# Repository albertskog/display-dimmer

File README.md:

# Display Dimmer

A pair of physical buttons to control the brightness of a pair of external monitors over HDMI.

## Why?

My USB-C port replicator does not pass on brightness commands to my monitors.

## How?

HDMI has a control channel called DDC. Hook this board up to a spare HDMI port on a monitor and use the buttons to control the brightness.

# Hardware Considerations

Here are some design considerations that were taken into account.

## VCC Voltage

The board has a footprint for a 3.3 V regulator and also a footprint for a 0 Ohm bypass to use 5 V directly from USB. HDMI signaling is 5 V and the CH32V003 can run at 5 V, but both also work at 3.3 V. I have used the 5 V option.

## Pull-up Resistors

On my monitors, the I2C lines are already pulled up to 5 V internally. The PCB has footprints for additional pull-up, but I found it works fine without populating them.

## USB

The board has a USB connector for power. The data lines are connected to GPIO pins for possible future use.

> Only GPIOs 0-4 can be used for USB D+/D- due to limits of the [c.andi](https://msyksphinz-self.github.io/riscv-isadoc/html/rvc.html#c-andi) instruction which can only hold a 5 bit value.
> You **cannot use** PC5-PC7 and PD5-PD7 for D+/D-!

[GitHub - cnlohr/rv003usb: CH32V003 RISC-V Pure Software USB Controller](https://github.com/cnlohr/rv003usb)

## BOM

| Amount | Part                | Name         | Source                                                                  |
|--------|---------------------|--------------|-------------------------------------------------------------------------|
| 1x     | MCU                 | CH32V003F4P6 | WCH on Aliexpress                                                       |
| 2x     | HDMI connector      | 685119134923 | [Electrokit](https://www.electrokit.com/hdmi-hona-19p-pcb-smd-wrth)     |
| 1x     | Micro USB connector | 629105136821 | [Electrokit](https://www.electrokit.com/usb-micro-b-kontakt-smd)        |
| 2x     | Buttons             | MX-style     |                                                                         |
| 1x     | Fuse                | 1206L025YR   | [Electrokit](https://www.electrokit.com/polyswitch-16v-0.25a-smd)       |
| 4x     | Protection resistor | 1206 22R     |                                                                         |
| 2x     | ESD protection      | NUP2105LT1G  | [Electrokit](https://www.electrokit.com/nup2105lt1g-sot23-3-tvs-diod)   |
| 1x     | 5 V bypass          | 1206 0R      |                                                                         |

### Not mounted

| Amount | Part                | Name         | Source                                                                                    |
|--------|---------------------|--------------|-------------------------------------------------------------------------------------------|
| 4x     | Pull-up resistor    | 1206 10K     |                                                                                           |
| 1x     | 3.3 V LDO           | LDI1117-3.3H | [Electrokit](https://www.electrokit.com/ldi1117-3.3h-sot-223-spanningsregulator-ldo-3.3v) |
| 1x     | Crystal 24 MHz      | HC49/U4H     | [Electrokit](https://www.electrokit.com/kristall-24.000mhz-smd-hc49/u4h)                  |

# Firmware

There are three firmware options:

1. The proof-of-concept written in Micropython on a Raspberry Pi RP2040.
2. The prototype firmware written in Platformio/Arduino C++ on a WCH CH32V003 devkit.
3. The final firmware written in Rust on the custom PCB.

## DDC Commands

DDC commands are hard-coded in the firmware. The payloads were generated from a slightly modified version of [python-ddcci](https://github.com/Informatic/python-ddcci)

| Command       | Data                                          |
|---------------|-----------------------------------------------|
| Set 0%        | `[0x51, 0x84, 0x3, 0x10, 0x0, 0x0, 0xa8]`     |
| Set 10%       | `[0x51, 0x84, 0x3, 0x10, 0x0, 0xa, 0xa2]`     |
| Set 20%       | `[0x51, 0x84, 0x3, 0x10, 0x0, 0x14, 0xbc]`    |
| Set 30%       | `[0x51, 0x84, 0x3, 0x10, 0x0, 0x1e, 0xb6]`    |
| Set 40%       | `[0x51, 0x84, 0x3, 0x10, 0x0, 0x28, 0x80]`    |
| Set 50%       | `[0x51, 0x84, 0x3, 0x10, 0x0, 0x32, 0x9a]`    |
| Set 60%       | `[0x51, 0x84, 0x3, 0x10, 0x0, 0x3c, 0x94]`    |
| Set 70%       | `[0x51, 0x84, 0x3, 0x10, 0x0, 0x46, 0xee]`    |
| Set 80%       | `[0x51, 0x84, 0x3, 0x10, 0x0, 0x50, 0xf8]`    |
| Set 90%       | `[0x51, 0x84, 0x3, 0x10, 0x0, 0x5a, 0xf2]`    |
| Set 100%      | `[0x51, 0x84, 0x3, 0x10, 0x0, 0x64, 0xcc]`    |
| Get (not used)| `[0x51, 0x82, 0x1, 0x10, 0xad]`               |

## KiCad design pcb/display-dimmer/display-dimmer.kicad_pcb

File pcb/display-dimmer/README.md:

# Display Dimmer PCB

This folder contains the Kicad project files for the Display Dimmer PCB.

Unfortunatley, a couple of footprints from SnapEDA were used without realizing their license does not permit sharing. You will need to download them separatley:

- USB connector: https://www.digikey.se/en/models/2627271
- HDMI connector: https://www.digikey.se/en/models/2508506

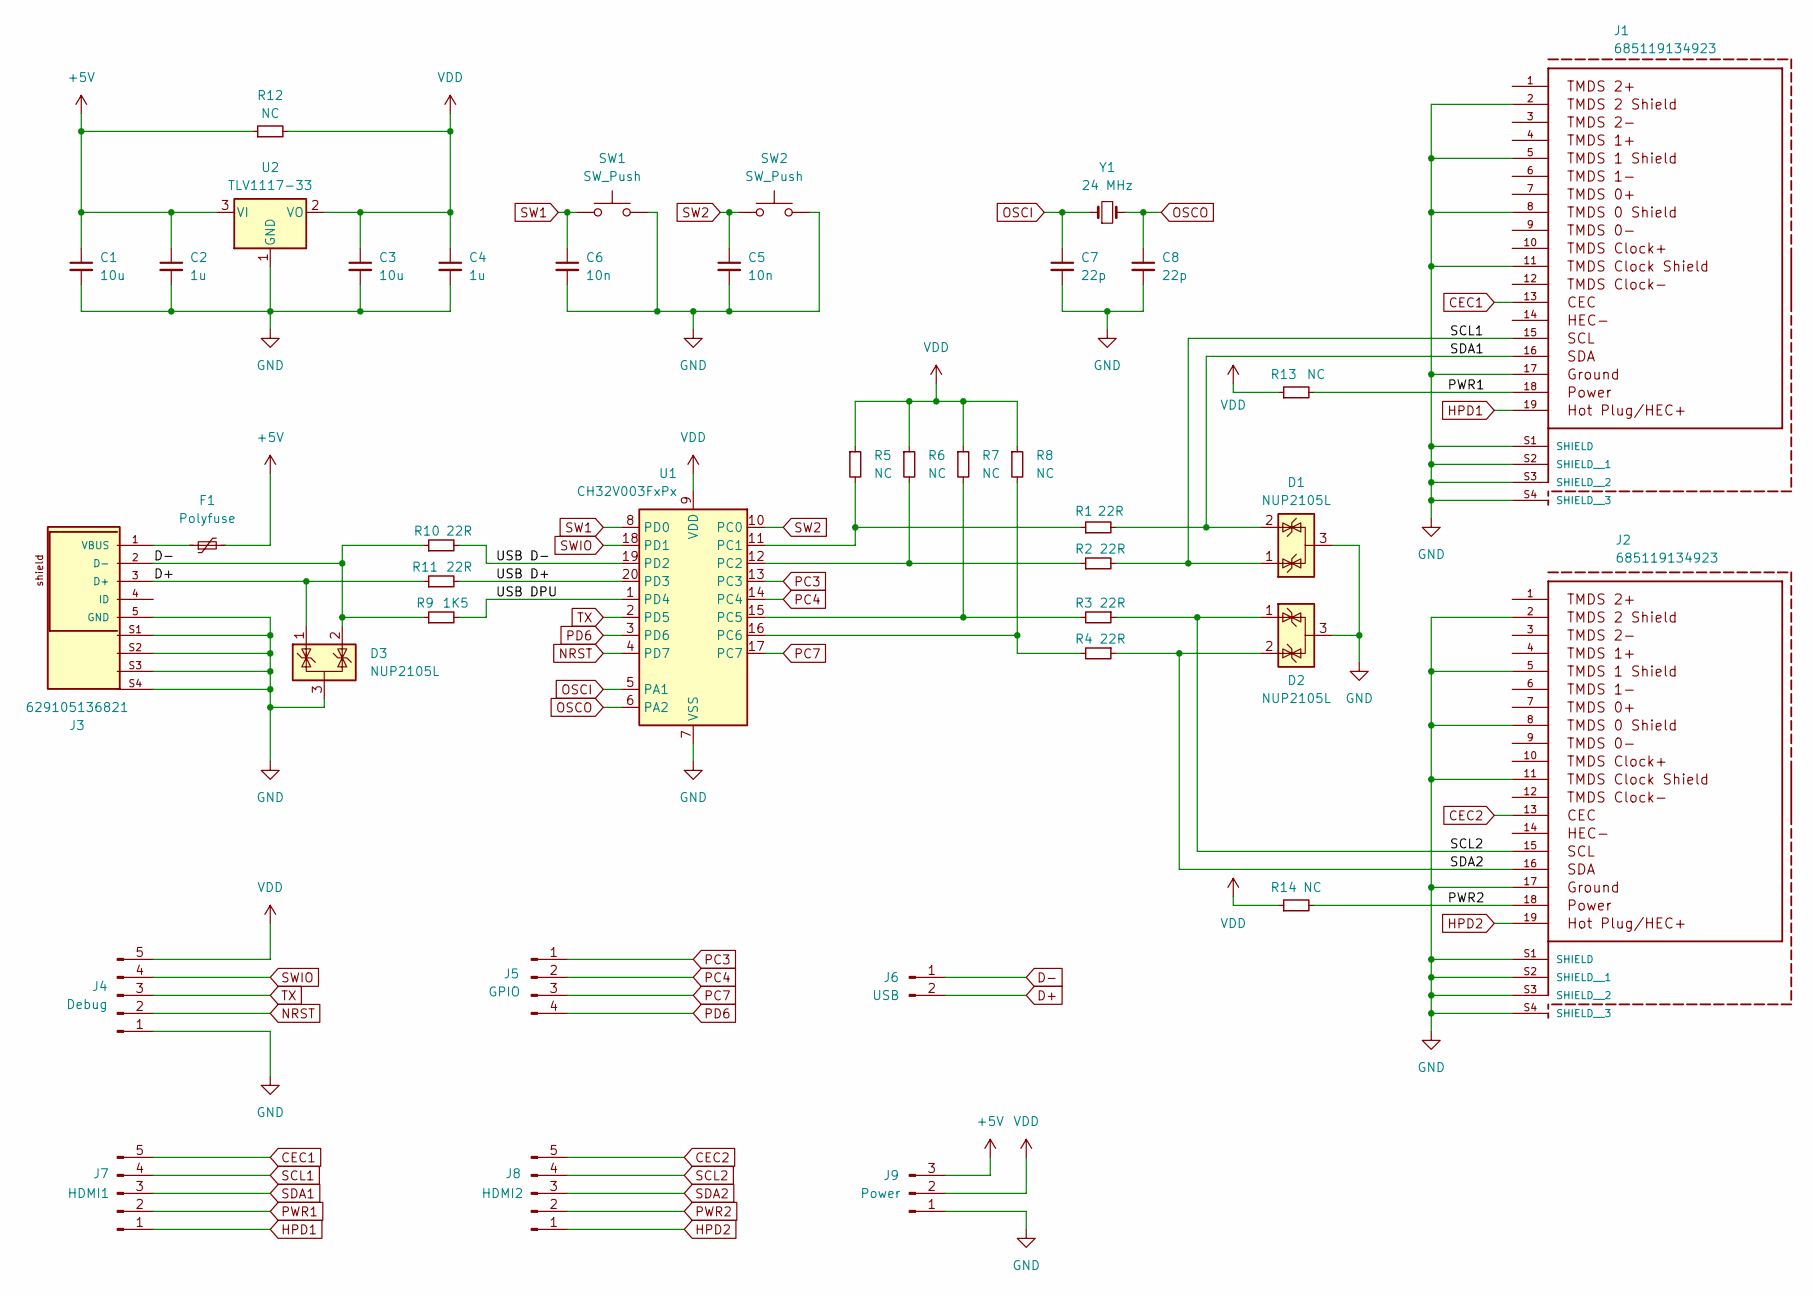
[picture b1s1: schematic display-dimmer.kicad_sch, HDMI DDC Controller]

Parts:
C1, C3: 10u; C_1206_3216Metric_Pad1.33x1.80mm_HandSolder
C2, C4: 1u; C_1206_3216Metric_Pad1.33x1.80mm_HandSolder
C5, C6: 10n; C_1206_3216Metric_Pad1.33x1.80mm_HandSolder
C7, C8: 22p; C_1206_3216Metric_Pad1.33x1.80mm_HandSolder
D1, D2, D3: NUP2105L; SOT-23
F1: Polyfuse; Fuse_1206_3216Metric_Pad1.42x1.75mm_HandSolder
J1, J2: 685119134923; PART-NUMBER 685119134923
J3: 629105136821; PART-NUMBER 629105136821
J4: Debug; PinHeader_1x05_P2.54mm_Vertical
J5: GPIO; PinHeader_1x04_P2.54mm_Vertical
J6: USB; PinHeader_1x02_P2.54mm_Vertical
J7: HDMI1; PinHeader_1x05_P2.54mm_Vertical
J8: HDMI2; PinHeader_1x05_P2.54mm_Vertical
J9: Power; PinHeader_1x03_P2.54mm_Vertical
R1, R2, R3, R4, R10, R11: 22R; R_1206_3216Metric_Pad1.30x1.75mm_HandSolder
R5, R6, R7, R8, R12, R13, R14: NC; R_1206_3216Metric_Pad1.30x1.75mm_HandSolder
R9: 1K5; R_1206_3216Metric_Pad1.30x1.75mm_HandSolder
SW1, SW2: SW_Push; SW_Cherry_MX_1.00u_PCB
U1: CH32V003FxPx; TSSOP-20_4.4x6.5mm_P0.65mm
U2: TLV1117-33; SOT-223-3_TabPin2
Y1: 24 MHz; Crystal_SMD_HC49-SD_HandSoldering

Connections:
+5V: C1.1, C2.1, F1.2, J9.3, R12.1, U2.3 (VI)
/USB D+: R11.2, U1.20 (PD3)
/USB D-: R10.2, U1.19 (PD2)
/USB DPU: R9.2, U1.1 (PD4)
CEC1: J1.13, J7.5
CEC2: J2.13, J8.5
D+: D3.1 (K), J3.3 (D+), J6.2, R11.1
D-: D3.2 (K), J3.2 (D-), J6.1, R9.1, R10.1
GND: C1.2, C2.2, C3.2, C4.2, C5.2, C6.2, C7.2, C8.2, D1.3 (A), D2.3 (A), D3.3 (A), J1.2, J1.5, J1.8, J1.11, J1.17, J1.S1 (SHIELD), J1.S2 (SHIELD__1), J1.S3 (SHIELD__2), J1.S4 (SHIELD__3), J2.2, J2.5, J2.8, J2.11, J2.17, J2.S1 (SHIELD), J2.S2 (SHIELD__1), J2.S3 (SHIELD__2), J2.S4 (SHIELD__3), J3.5 (GND), J3.S1, J3.S2, J3.S3, J3.S4, J4.1, J9.1, SW1.2, SW2.2, U1.7 (VSS), U2.1 (GND)
HPD1: J1.19, J7.1
HPD2: J2.19, J8.1
NRST: J4.2, U1.4 (PD7)
unnamed: F1.1, J3.1 (VBUS)
unnamed: R1.1, R5.2, U1.11 (PC1)
unnamed: R2.1, R6.2, U1.12 (PC2)
unnamed: R3.2, R7.2, U1.15 (PC5)
unnamed: R4.2, R8.2, U1.16 (PC6)
OSCI: C7.1, U1.5 (PA1), Y1.1
OSCO: C8.1, U1.6 (PA2), Y1.2
PC3: J5.1, U1.13 (PC3)
PC4: J5.2, U1.14 (PC4)
PC7: J5.3, U1.17 (PC7)
PD6: J5.4, U1.3 (PD6)
PWR1: J1.18, J7.2, R13.2
PWR2: J2.18, J8.2, R14.2
SCL1: D1.1 (K), J1.15, J7.4, R2.2
SCL2: D2.1 (K), J2.15, J8.4, R3.1
SDA1: D1.2 (K), J1.16, J7.3, R1.2
SDA2: D2.2 (K), J2.16, J8.3, R4.1
SW1: C6.1, SW1.1, U1.8 (PD0)
SW2: C5.1, SW2.1, U1.10 (PC0)
SWIO: J4.4, U1.18 (PD1)
TX: J4.3, U1.2 (PD5)
VDD: C3.1, C4.1, J4.5, J9.2, R5.1, R6.1, R7.1, R8.1, R12.2, R13.1, R14.1, U1.9 (VDD), U2.2 (VO)

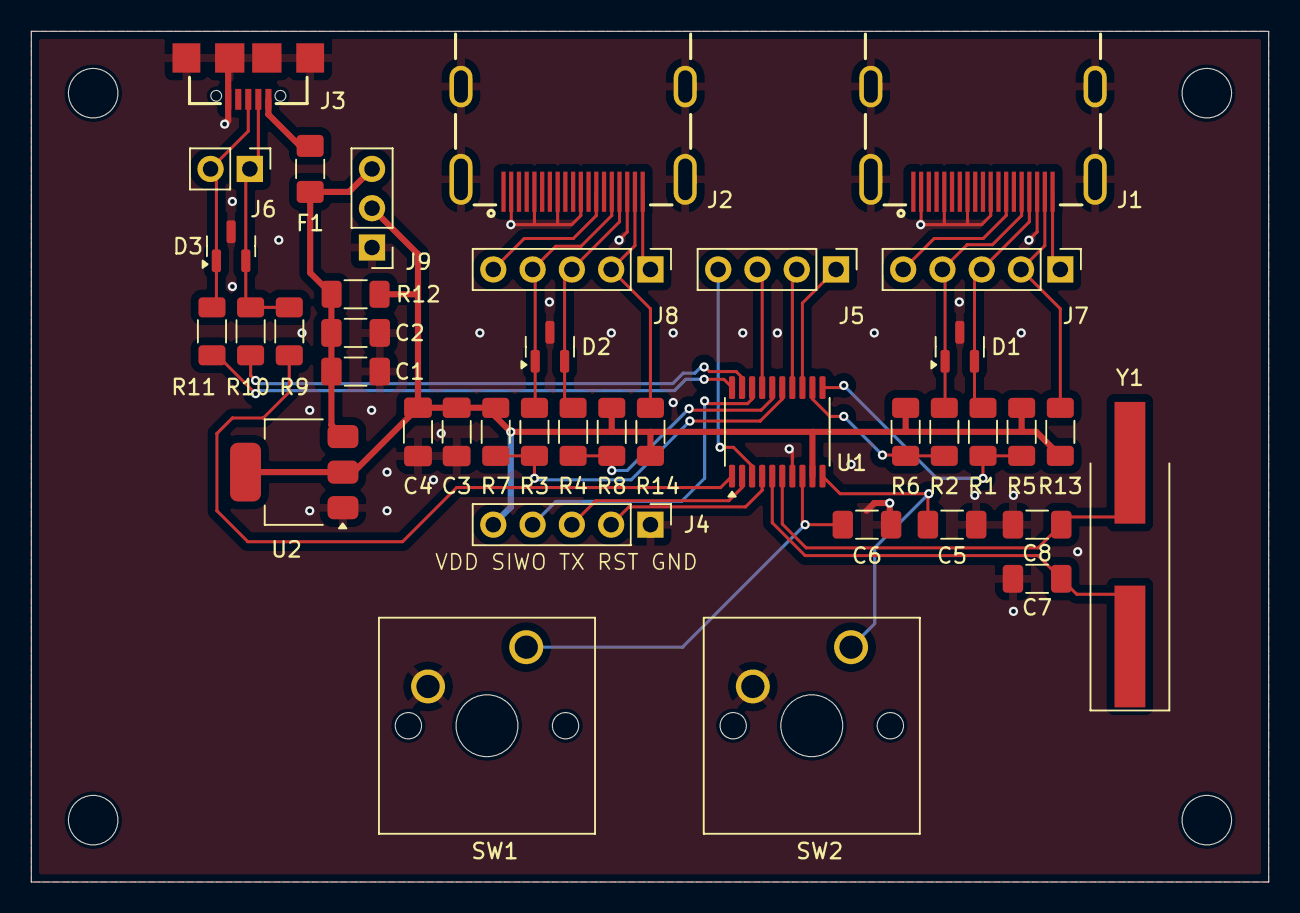
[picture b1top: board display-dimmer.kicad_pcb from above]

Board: 2 copper layers, 80.0 x 55.0 mm, 40 parts (0 on the bottom side), 34 nets.

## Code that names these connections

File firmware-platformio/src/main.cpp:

#include <Arduino.h>
#include <Wire.h>

#define PLUS PD0
#define MINUS PC0

#define ADDRESS 0x37

// Pre-computed commands for 0-100% brightness
uint8_t commands[11][7] = {
    {0x51, 0x84, 0x03, 0x10, 0x00, 0x00, 0xa8},
    {0x51, 0x84, 0x03, 0x10, 0x00, 0x0a, 0xa2},
    {0x51, 0x84, 0x03, 0x10, 0x00, 0x14, 0xbc},
    {0x51, 0x84, 0x03, 0x10, 0x00, 0x1e, 0xb6},
    {0x51, 0x84, 0x03, 0x10, 0x00, 0x28, 0x80},
    {0x51, 0x84, 0x03, 0x10, 0x00, 0x32, 0x9a},
    {0x51, 0x84, 0x03, 0x10, 0x00, 0x3c, 0x94},
    {0x51, 0x84, 0x03, 0x10, 0x00, 0x46, 0xee},
    {0x51, 0x84, 0x03, 0x10, 0x00, 0x50, 0xf8},
    {0x51, 0x84, 0x03, 0x10, 0x00, 0x5a, 0xf2},
    {0x51, 0x84, 0x03, 0x10, 0x00, 0x64, 0xcc}
};

TwoWire Display_A = TwoWire((uint32_t)PC1, (uint32_t)PC2);
TwoWire Display_B = TwoWire((uint32_t)PC6, (uint32_t)PC5);

int8_t brightness = 5;
int8_t change = 0;

void set(uint8_t *command){
    Display_A.begin((uint32_t)PC1, (uint32_t)PC2);
    Display_A.beginTransmission(ADDRESS);
    Display_A.write(command, 7);
    Display_A.endTransmission(true);
    Display_A.end();

    Display_B.begin((uint32_t)PC6, (uint32_t)PC5);
    Display_B.beginTransmission(ADDRESS);
    Display_B.write(command, 7);
    Display_B.endTransmission(true);
    Display_B.end();
}

void setup(){
    pinMode(PLUS, INPUT_PULLUP);
    pinMode(MINUS, INPUT_PULLUP);
}

void loop(){
    int8_t new_change = digitalRead(PLUS) - digitalRead(MINUS);

    if (new_change == 0){
        change = 0;
        return;
    }

    // Detect press and hold
    if (change == new_change){
        change = new_change * 10;
    }
    else {
        change = new_change;
    }

    int8_t new_brightness = constrain(brightness + change, 0, 10);
    
    if(brightness != new_brightness) {
        brightness = new_brightness;
        set(commands[brightness]);
    }

    delay(300);
}

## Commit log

2024-11-12 Add project files
2024-11-14 Remove unused variable
2024-11-14 Add readme, update gitignore
2024-11-14 Add patched Arduino core to config file and add readme
2024-11-14 Update gitignore files
